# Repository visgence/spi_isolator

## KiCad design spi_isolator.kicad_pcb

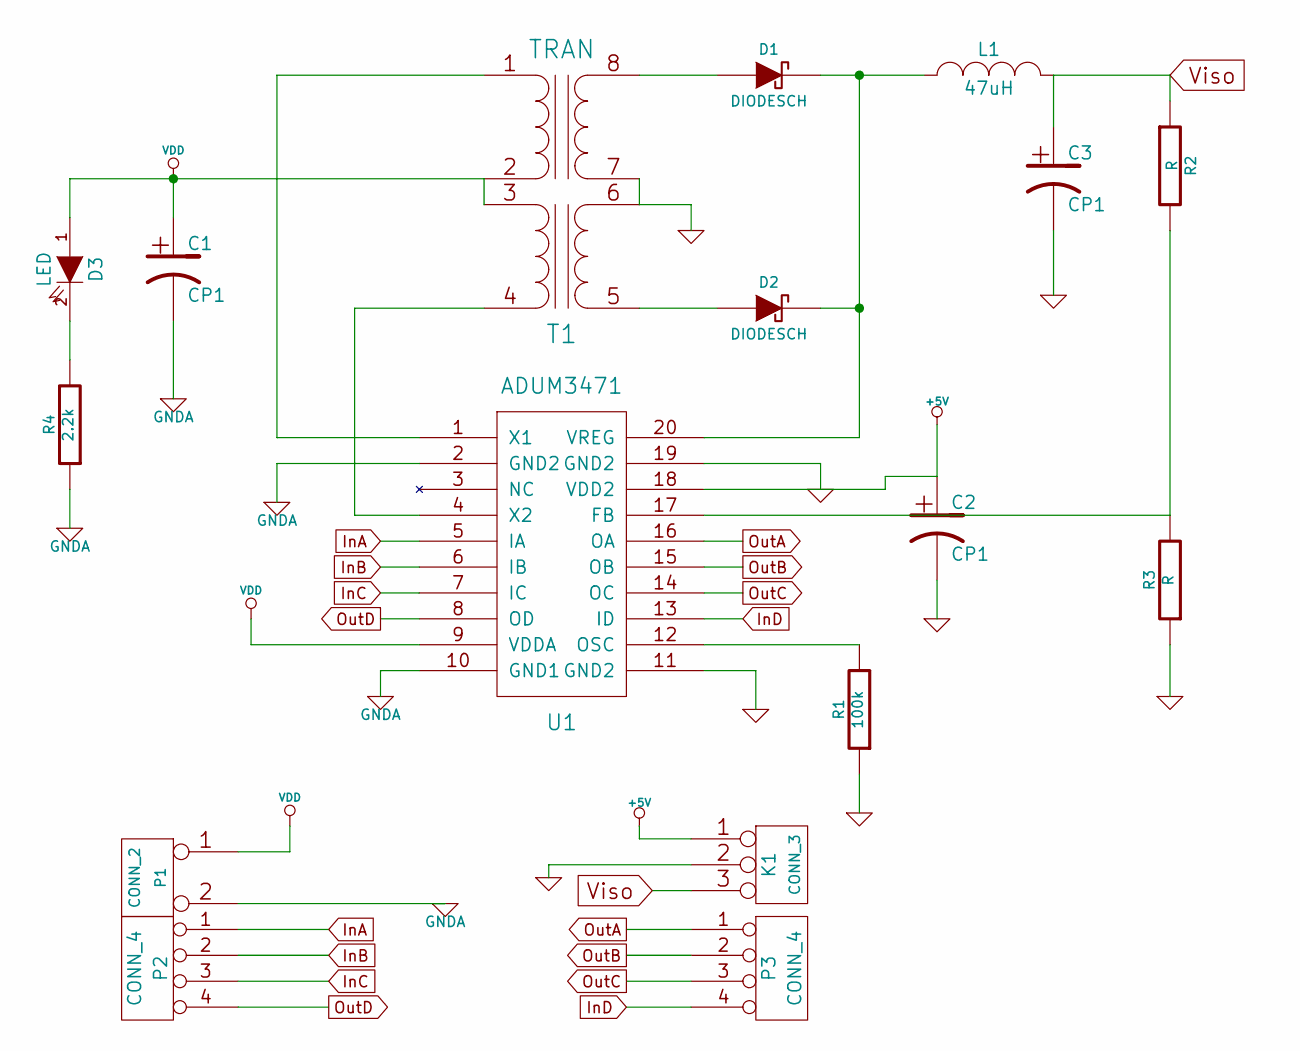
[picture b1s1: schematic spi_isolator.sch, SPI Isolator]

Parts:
C1, C2, C3: CP1
D1, D2: DIODESCH
D3: LED
K1: CONN_3
L1: 47uH
P1: CONN_2
P2, P3: CONN_4
R1: 100k
R2, R3: R
R4: 2.2k
T1: TRAN
U1: ADUM3471

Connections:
GNDA: C1.2, P1.2 (PM), R4.1, U1.2 (GND2), U1.10 (GND1)
InA: P2.1, U1.5 (IA)
InB: P2.2, U1.6 (IB)
InC: P2.3, U1.7 (IC)
InD: P3.4, U1.13 (ID)
unnamed: R1.2, U1.12 (OSC)
unnamed: D3.2 (K), R4.2
unnamed: T1.1 (AA), U1.1 (X1)
unnamed: T1.4 (AB), U1.4 (X2)
unnamed: R2.2, R3.2, U1.17 (FB)
unnamed: D1.1 (A), T1.8 (SB)
unnamed: D2.1 (A), T1.5 (SA)
unnamed: D1.2 (K), D2.2 (K), L1.1, U1.20 (VREG)
OutA: P3.1, U1.16 (OA)
OutB: P3.2, U1.15 (OB)
OutC: P3.3, U1.14 (OC)
OutD: P2.4, U1.8 (OD)
VDD: C1.1, D3.1 (A), P1.1, T1.2 (AB), T1.3 (AA), U1.9 (VDDA)
Viso: C3.1, K1.3, L1.2, R2.1

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
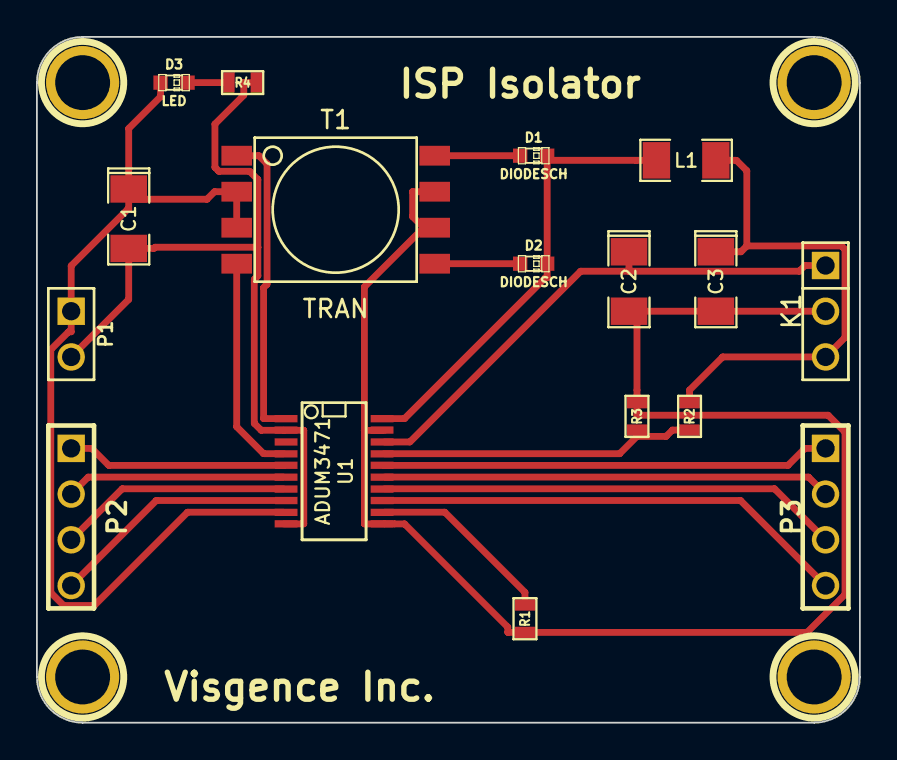
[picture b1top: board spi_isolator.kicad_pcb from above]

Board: 2 copper layers, 45.7 x 38.1 mm, 21 parts (0 on the bottom side), 21 nets.

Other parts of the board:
h1: h1; 1pin
h2: h2; 1pin
h3: h3; 1pin
h4: h4; 1pin

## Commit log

2013-11-09 Changed part on board
